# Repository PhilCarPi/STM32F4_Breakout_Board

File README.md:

# STM32F4_Breakout_Board
4 layer PCB that serves as a breakout board to an STM32F405 chip with an additional IMU chip just for fun. The breakout is for serial ports SPI, USART, I2C, and SWD.

## Front

## Back

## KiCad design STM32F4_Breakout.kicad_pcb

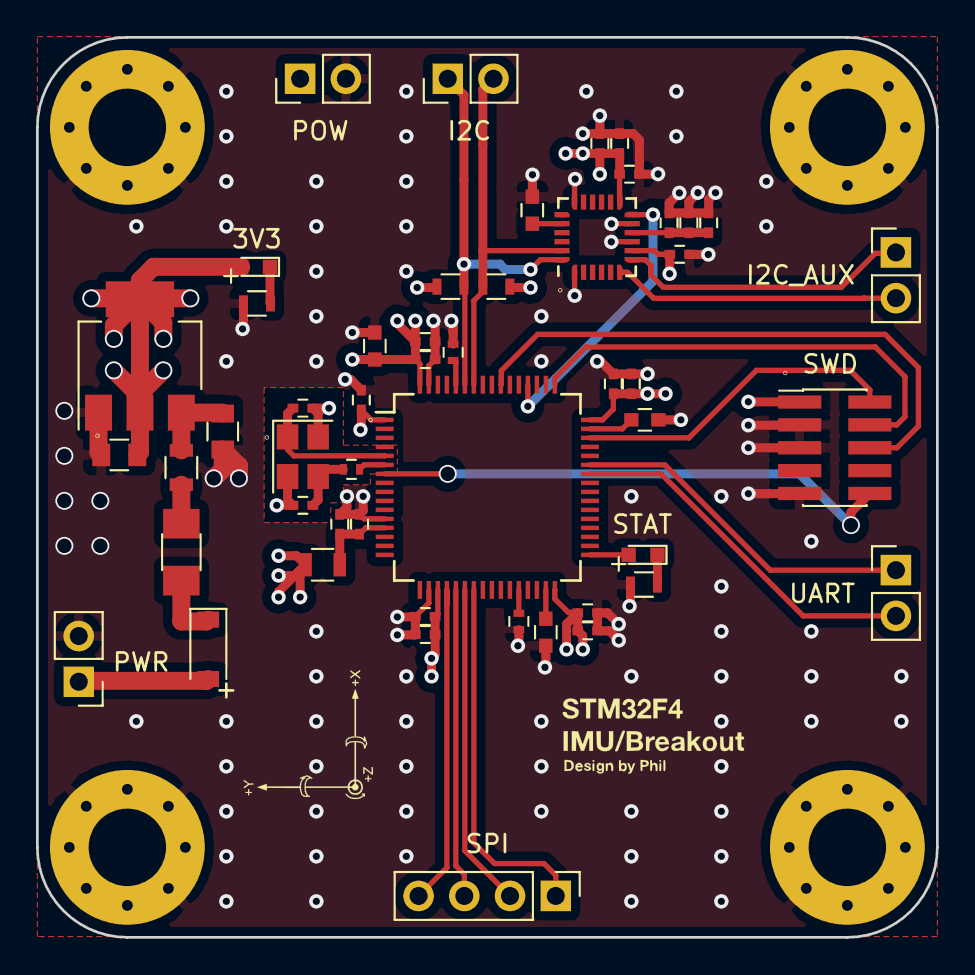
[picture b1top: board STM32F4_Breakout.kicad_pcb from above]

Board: 4 copper layers, 50.0 x 50.0 mm, 54 parts (0 on the bottom side), 34 nets.

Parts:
C1, C2: 10uF; C_0805
C3: 10uF; C_0603
C4, C5, C6, C7, C8, C9, C10, C11, C12, C15: 100nF; C_0402
C13, C14: 12pF; C_0402
C16, C19: 10nF; C_0402
C17, C18: 2.2uF; C_0603
C20, C21, C23, C24, C25, C26: 33nF; C_0402
C22: 2.2nF; C_0603
D1: B5819W; D_SOD-123
D2: Green; LED_0603
D3: Blue; LED_0603
F1: 500mA; Fuse_SMD1206_Wave
FB1, FB2: 100 @ 100Mhz; L_0805
H1, H2, H3, H4: MountingHole_Pad; MountingHole_4.3mm_M4_Pad_Via
HSE1: 16MHz; Crystal_SMD_3225-4pin_3.2x2.5mm
J1, J2, J3, J5, J7: Conn_01x02; Pin_Header_Straight_1x02_Pitch2.54mm
J4: Conn_02x05_Odd_Even; Pin_Header_Straight_2x05_Pitch1.27mm_SMD
J6: Conn_01x04; Pin_Header_Straight_1x04_Pitch2.54mm
R1, R3, R4, R7: 2k2; R_0603
R2: 220; R_0402
R5, R6: 10k; R_0402
U1: AMS1117-3.3; SOT-223-3_TabPin2
U2: STM32F405RGT6; LQFP-64_10x10mm_Pitch0.5mm
U3: MPU-6050; QFN-24_4x4mm_Pitch0.5mm

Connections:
+3.3VA: C15.1, C16.1, FB2.1, U2.13
+3V3: C2.1, C3.1, C4.1, C5.1, C6.1, C7.1, C8.1, C9.1, C10.1, C11.1, C12.1, C19.1, C20.1, C23.1, C24.1, D2.2, FB2.2, J3.1, J4.1, R3.2, R4.2, U1.2, U2.1, U2.19, U2.32, U2.48, U2.64, U3.8, U3.13
AUX_SCL: J7.1, U3.7
AUX_SDA: J7.2, U3.6
BOOT0: R5.1, U2.60
BOOT1: R6.1, U2.28
GND: C1.2, C2.2, C3.2, C4.2, C5.2, C6.2, C7.2, C8.2, C9.2, C10.2, C11.2, C12.2, C13.2, C14.2, C15.2, C16.2, C17.2, C18.2, C19.2, C20.2, C21.2, C22.2, C23.2, C24.2, C25.2, C26.2, H1.1, H2.1, H3.1, H4.1, HSE1.2, HSE1.4, J2.2, J3.2, J4.3, J4.5, J4.9, R1.1, R5.2, R6.2, R7.1, U1.1, U2.12, U2.18, U2.63, U3.1, U3.9, U3.11, U3.18
HSE_IN: C13.1, HSE1.1, U2.5
HSE_OUT: R2.1, U2.6
I2C1_SCL: J5.2, R4.1, U2.58, U3.23
I2C1_SDA: J5.1, R3.1, U2.59, U3.24
INT: U2.52, U3.12
NRST: J4.10, U2.7
unnamed: C1.1, FB1.1, U1.3
unnamed: C14.1, HSE1.3, R2.2
unnamed: C17.1, U2.31
unnamed: C18.1, U2.47
unnamed: C21.1, C25.1, C26.1, U3.10
unnamed: C22.1, U3.20
unnamed: D1.1, F1.1
unnamed: D2.1, R1.2
unnamed: D3.1, R7.2
unnamed: D3.2, U2.33
unnamed: F1.2, FB1.2
SPI1_CS: J6.4, U2.20
SPI1_MISO: J6.2, U2.22
SPI1_MOSI: J6.1, U2.23
SPI1_SCK: J6.3, U2.21
SWCLK: J4.4, U2.49
SWDIO: J4.2, U2.46
SWO: J4.6, U2.55
USART1_RX: J1.1, U2.43
USART1_TX: J1.2, U2.42
VCC: D1.2, J2.1

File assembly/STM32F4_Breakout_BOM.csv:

Designator,Quantity,Value,Footprint,LCSC Part #
"C1, C2, ",2,10uF,0805,C15850
"C3, ",1,10uF,0603,C19702
"C14, C13, ",2,12pF,0402,C1547
"C15, C4, C5, C6, C7, C8, C9, C10, C11, C12, ",10,100nF,0402,C1525
"C16, ",1,10nF,0402,C15195
"C17, C18, ",2,2.2uF,0603,C23630
"D1, ",1,B5819W,SOD-123,C8598
"D2, ",1,Green,0603,C72043
"D3, ",1,Blue,0603,C72041
"F1, ",1,500mA,1206,C163133
"FB1, FB2, ",2,100 @ 100Mhz,0805,C1015
"HSE1, ",1,16MHz,SMD-3225_4P,C13738
"R2, ",1,220,0402,C25091
"R5, R6, ",2,10k,0402,C25744
"R7, R1, R4, R3, ",4,2k2,0603,C4190
"U1, ",1,AMS1117-3.3,SOT-223,C6186
"U2, ",1,STM32F405RGT6,LQFP-64_10.0x10.0x0.5P,C15742

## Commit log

2020-12-27 Moved local files to remote repository.
2020-12-27 Added 3D model image of the board.
2020-12-28 Added image of 3D model of the back.
